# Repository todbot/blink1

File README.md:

blink(1) USB RGB LED
====================

"[blink(1)](https://blink1.thingm.com/) is a super status light:
it packs three dimensions of information
(color, brightness and pattern) into a single tiny package that fits into
any USB port on nearly every device. It makes it incredibly easy to connect
any data source in the cloud or on your computer to a full-color RGB LED so
you can know what's happening without checking any windows, going to any
websites or typing any commands." - Get a blink(1) at https://buy.thingm.com/

More technically, blink(1) is a Smart LED controller with built-in USB firmware. blink(1) has a huge range of support from the Linux kernel to Node.js.

The officially supported repositories for blink(1) software are:

| repository | description |
| ---------- | ----------- |
| [Blink1Control2](https://github.com/todbot/Blink1Control2) | Graphical app for Mac / Windows / Linux |
| [blink1-tool](https://github.com/todbot/blink1-tool) | Command-line tool, simple API server, and C-library for all platforms |
| [blink1-python](https://pypi.org/project/blink1/) | Python library |
| [blink1rs](https://crates.io/crates/blink1rs) | Rust library |
| [node-blink1](https://www.npmjs.com/package/node-blink1) | Node.js library |
| [blink1-java](https://github.com/todbot/blink1-java) | Java and Processing library |
| [go-blink1](https://github.com/todbot/go-blink1) | Go library |
| [blink1-android](https://github.com/todbot/blink1-android) | Android library |
| [blink1-webhid](https://github.com/todbot/blink1-webhid) | WebHID demos for blink(1) |
| [blink1mk3](https://github.com/todbot/blink1mk3) | Hardware/firmware design for blink(1) mk3 |
| [blink1](https://github.com/todbot/blink1) | Hardware/firmware design, misc docs & notes (this repo) |

Other instructive examples: 

| repository | description |
| ---------- | ----------- |
| [electron-blink1-toy](https://github.com/todbot/electron-blink1-toy/) | Simplest possible Electron app for controlling blink(1) |
| [tauri-blink1-toy](https://github.com/todbot/tauri-blink1-toy/) | Simplest possible Tauri/Rust app for controlling blink(1) |

See each project for details, including APIs for languages not mentioned.

This repo used to house all blink(1)-related code, but is now a clearinghouse and links to official and supported blink(1) repositories.

## Blink1Control2 ##

[Blink1Control2](https://github.com/todbot/Blink1Control2) is an application for controlling and hooking events to blink(1). It is the primary user-level application for controlling blink(1).
It is an event-based system for triggering blink(1) color patterns.
Those events can be on your computer or on the Net.

Blink1Control2 can receive events from:
- [IFTTT](https://ifttt.com/channels)'s many channels
- IMAP/GMAIL email services
- Skype events
- URLs containing text or JSON
- Local files or executed scripts

Blink1Control2 has its own repository. More information at:
https://github.com/todbot/Blink1Control2

#### Download Blink1Control2 ####
- Mac OS X: https://github.com/todbot/Blink1Control2/releases
- Windows: https://github.com/todbot/Blink1Control2/releases

## blink1-tool ##

`blink1-tool` is a C-based command-line for script-writers, programmers and hackers. It lives in the [blink1-tool repo]( https://github.com/todbot/blink1-tool):

The repo contains several useful tools:

- **blink1-tool** -- command-line program for use in your own scripts
- **blink1-tiny-server** -- simple RESTish JSON API server for controlling blink(1)s
- **blink1control-tool** -- control blink(1) through Blink1Controll app as if with blink1-tool

--- 

--- 

## What is in *this* repo ##

Most code in this repo is **deprecated** but kept around for historical interest.

- __docs__             -- Documentation of APIs and tips & tricks
- __java__             -- Java / Processing library info
- __processing__       -- Processing applications  (https://processing.org)
- __nodejs__           -- NodeJs library info
- __python__           -- Python libraries (there are a couple to choose from)
- __ruby__             -- Ruby APIs & Ruby Tools
- __go__               -- Go library
- __qt__               -- old Blink1Control1 Qt app
- __mac__              -- Mac OS X details and old Blink1Control0 app
  - scripts      -- command-line scripts to do cool things
- __windows__          -- Windows and .NET details and old Blink1Control0 app
  - Blink1Lib     -- .NET library wrapping blink1-lib 
  - ManagedBlink1 -- 100% .NET library, supercedd by [Sleddog.Blink1](https://github.com/SleddogSoftwareDevelopment/blink1)
  - scripts  -- Windows command-line scripts to do cool things
- __linux__            -- Linux details and scripts
  - contrib__    -- contributed Linux scripts
- __chrome__           -- ChromeOS info
- __hardware__         -- all hardware-related info (firmware & schematic & enclosure)

Useful docs
-------------

- [blink1-tool usage](https://github.com/todbot/blink1-tool/#commmand-line-options-for-blink1-tool)
- [app-url-api-examples](https://github.com/todbot/blink1/blob/master/docs/app-url-api-examples.md)
- [app-url-api](https://github.com/todbot/blink1/blob/master/docs/app-url-api.md)

Also see the [wiki pages](https://github.com/todbot/blink1/wiki/_pages)

# Copyright and License

blink(1) is open source hardware OSHW US000051

Copyright (c) ThingM, 2012-2018

'blink(1)' is a trademark of ThingM Corporation

License: CC BY-SA 3.0
https://creativecommons.org/licenses/by-sa/3.0/

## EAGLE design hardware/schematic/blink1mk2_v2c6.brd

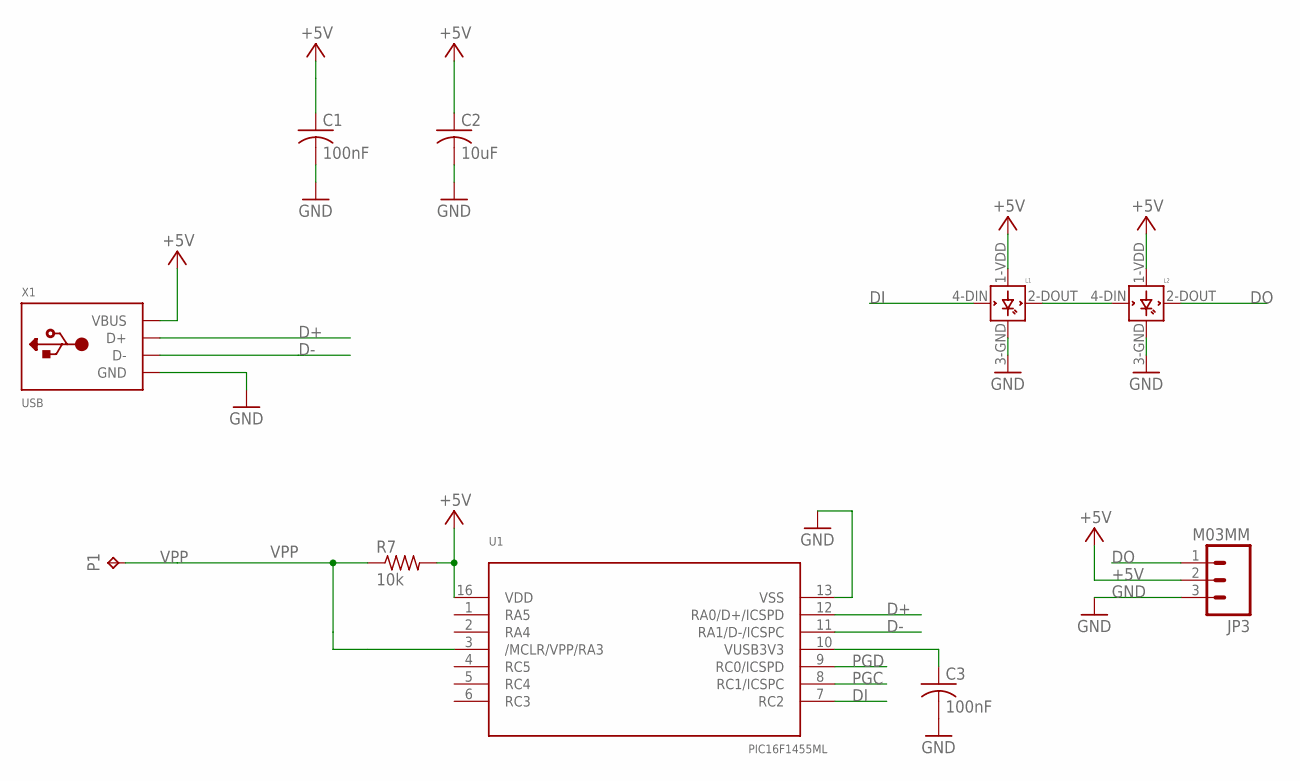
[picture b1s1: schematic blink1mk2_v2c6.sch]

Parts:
C1, C3: 100nF; C0603
C2: 10uF; C0603
JP3: M03MM; 1X03-1.5MM
L1, L2: WS2812B
P1: TPTP11SQ; TP11SQ
R7: 10k; R0603
U1: PIC16F1455ML; QFN16_4X4
X1: USB; MOLEX-48037-1000

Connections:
+5V: C1.1, C2.1, JP3.2, L1.1-VDD (VDD), L2.1-VDD (VDD), R7.2, U1.16 (VDD), X1.1 (VBUS)
D+: U1.12 (RA0/D+/ICSPD), X1.3 (D+)
D-: U1.11 (RA1/D-/ICSPC), X1.2 (D-)
DI: L1.4-DIN (DIN), U1.7 (RC2)
DO: JP3.1, L2.2-DOUT (DOUT)
GND: C1.2, C2.2, C3.2, JP3.3, L1.3-GND (GND), L2.3-GND (GND), U1.13 (VSS), X1.4 (GND)
unnamed: L1.2-DOUT (DOUT), L2.4-DIN (DIN)
PGC: U1.8 (RC1/ICSPC)
PGD: U1.9 (RC0/ICSPD)
VPP: P1.TP, R7.1, U1.3 (/MCLR/VPP/RA3)
VUSB3V3: C3.1, U1.10 (VUSB3V3)

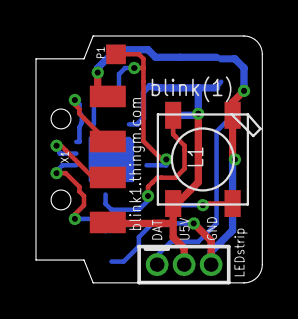
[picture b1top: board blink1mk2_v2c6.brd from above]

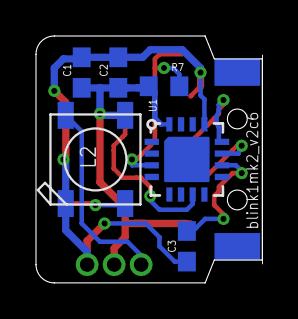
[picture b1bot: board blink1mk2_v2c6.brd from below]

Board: 2 copper layers, 12.6 x 13.7 mm, 10 parts (6 on the bottom side), 9 nets.

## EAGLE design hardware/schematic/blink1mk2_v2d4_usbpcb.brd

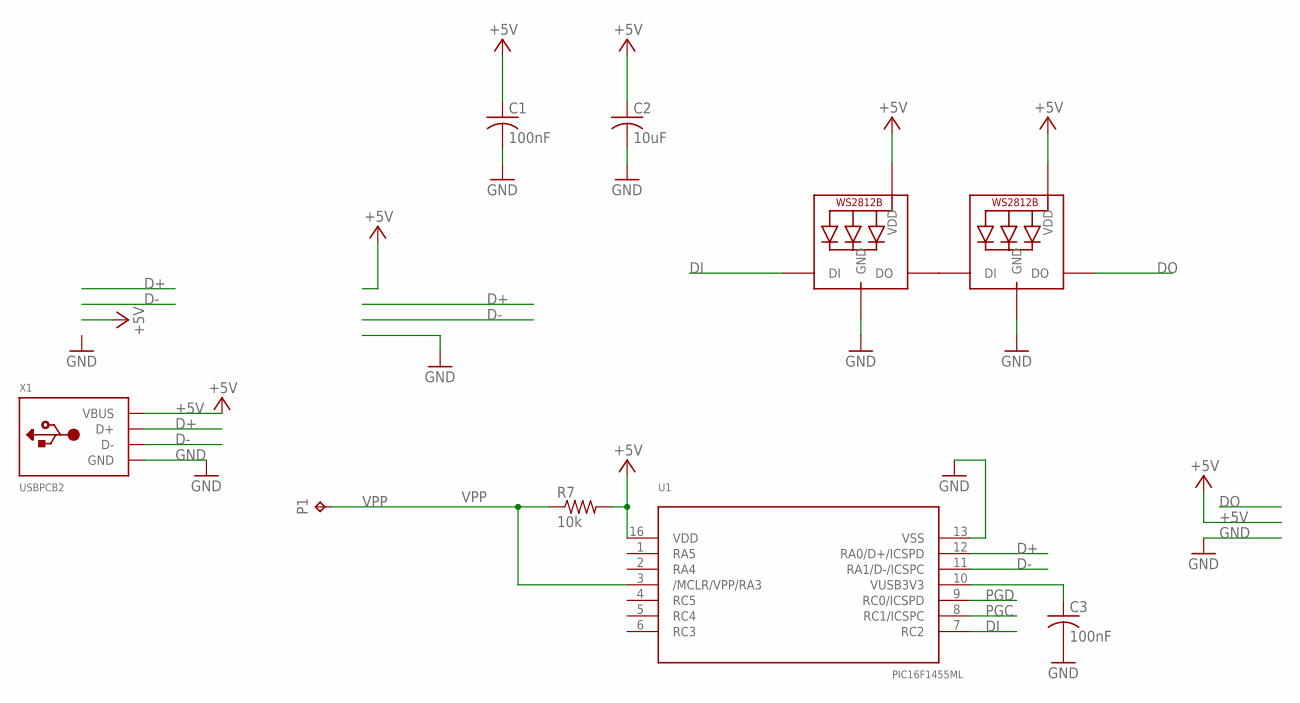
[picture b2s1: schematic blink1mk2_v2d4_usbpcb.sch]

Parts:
C1, C3: 100nF; C0603
C2: 10uF; C0603
LED1, LED2: WS2812B4020SIDE; SK6812-SIDE
P1: TPTP11SQ; TP11SQ
R7: 10k; R0603
U1: PIC16F1455ML; QFN16_4X4
X1: USBPCB2; USB-A-PCB-2

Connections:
+5V: C1.1, C2.1, LED1.1-VDD (VDD), LED2.1-VDD (VDD), R7.2, U1.16 (VDD), X1.5V (VBUS)
D+: U1.12 (RA0/D+/ICSPD), X1.USB_P (D+)
D-: U1.11 (RA1/D-/ICSPC), X1.USB_M (D-)
DI: LED1.4-DIN (DI), U1.7 (RC2)
DO: LED2.2-DOUT (DO)
GND: C1.2, C2.2, C3.2, LED1.3-GND (GND), LED2.3-GND (GND), U1.13 (VSS), X1.GND
unnamed: LED1.2-DOUT (DO), LED2.4-DIN (DI)
PGC: U1.8 (RC1/ICSPC)
PGD: U1.9 (RC0/ICSPD)
VPP: P1.TP, R7.1, U1.3 (/MCLR/VPP/RA3)
VUSB3V3: C3.1, U1.10 (VUSB3V3)

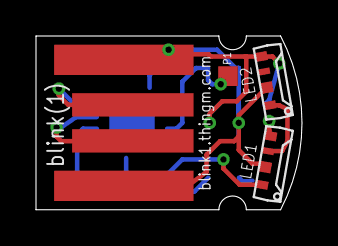
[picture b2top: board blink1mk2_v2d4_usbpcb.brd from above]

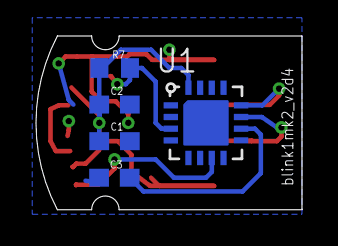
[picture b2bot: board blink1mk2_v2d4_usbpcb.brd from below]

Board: 2 copper layers, 14.8 x 9.7 mm, 9 parts (5 on the bottom side), 8 nets.

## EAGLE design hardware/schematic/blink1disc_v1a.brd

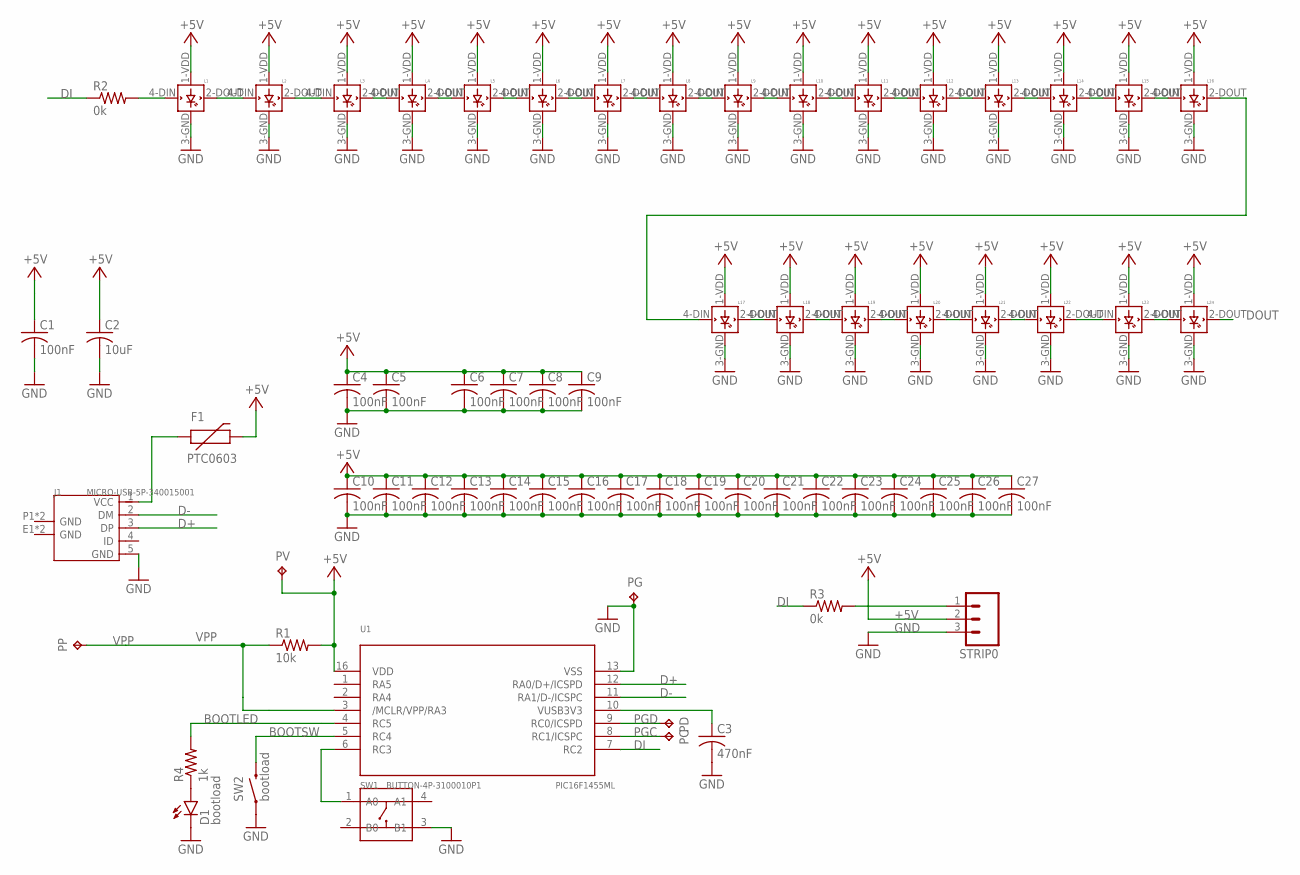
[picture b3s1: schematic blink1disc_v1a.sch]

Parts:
C1, C4, C5, C6, C7, C8, C9, C10, C11, C12, C13, C14, C15, C16, C17, C18, C19, C20, C21, C22, C23, C24, C25, C26, C27: 100nF; C0603
C2: 10uF; C0603
C3: 470nF; C0603
D1: bootload; LED-0603
F1: PTC0603; 0603
J1: MICRO-USB-5P-340015001; B-SMD-5P
L1, L2, L3, L4, L5, L6, L7, L8, L9, L10, L11, L12, L13, L14, L15, L16, L17, L18, L19, L20, L21, L22, L23, L24: WS2812B
PC: TPTP11SQ; TP11SQ
PD: TPTP11SQ; TP11SQ
PG: TPTP11SQ; TP11SQ
PP: TPTP11SQ; TP11SQ
PV: TPTP11SQ; TP11SQ
R1: 10k; R0603
R2, R3: 0k; R0603
R4: 1k; R0603
STRIP0: M03PTH; 1X03
SW1: BUTTON-4P-3100010P1; 4P-SMD-6.0X6.0X5.0H
SW2: bootload; TACTILE_SWITCH-SMD-RIGHT-ANGLE
U1: PIC16F1455ML; QFN16_4X4

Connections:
+5V: C1.1, C2.1, C4.1, C5.1, C6.1, C7.1, C8.1, C9.1, C10.1, C11.1, C12.1, C13.1, C14.1, C15.1, C16.1, C17.1, C18.1, C19.1, C20.1, C21.1, C22.1, C23.1, C24.1, C25.1, C26.1, C27.1, F1.2, L1.1-VDD (VDD), L2.1-VDD (VDD), L3.1-VDD (VDD), L4.1-VDD (VDD), L5.1-VDD (VDD), L6.1-VDD (VDD), L7.1-VDD (VDD), L8.1-VDD (VDD), L9.1-VDD (VDD), L10.1-VDD (VDD), L11.1-VDD (VDD), L12.1-VDD (VDD), L13.1-VDD (VDD), L14.1-VDD (VDD), L15.1-VDD (VDD), L16.1-VDD (VDD), L17.1-VDD (VDD), L18.1-VDD (VDD), L19.1-VDD (VDD), L20.1-VDD (VDD), L21.1-VDD (VDD), L22.1-VDD (VDD), L23.1-VDD (VDD), L24.1-VDD (VDD), PV.TP, R1.2, STRIP0.2, U1.16 (VDD)
BOOTLED: R4.2, U1.4 (RC5)
BOOTSW: SW2.2, U1.5 (RC4)
D+: J1.3 (DP), U1.12 (RA0/D+/ICSPD)
D-: J1.2 (DM), U1.11 (RA1/D-/ICSPC)
DI: R2.1, R3.1, U1.7 (RC2)
DO1: L2.2-DOUT (DOUT), L3.4-DIN (DIN)
DOUT: L24.2-DOUT (DOUT)
GND: C1.2, C2.2, C3.2, C4.2, C5.2, C6.2, C7.2, C8.2, C9.2, C10.2, C11.2, C12.2, C13.2, C14.2, C15.2, C16.2, C17.2, C18.2, C19.2, C20.2, C21.2, C22.2, C23.2, C24.2, C25.2, C26.2, C27.2, D1.C, J1.5 (GND), L1.3-GND (GND), L2.3-GND (GND), L3.3-GND (GND), L4.3-GND (GND), L5.3-GND (GND), L6.3-GND (GND), L7.3-GND (GND), L8.3-GND (GND), L9.3-GND (GND), L10.3-GND (GND), L11.3-GND (GND), L12.3-GND (GND), L13.3-GND (GND), L14.3-GND (GND), L15.3-GND (GND), L16.3-GND (GND), L17.3-GND (GND), L18.3-GND (GND), L19.3-GND (GND), L20.3-GND (GND), L21.3-GND (GND), L22.3-GND (GND), L23.3-GND (GND), L24.3-GND (GND), PG.TP, STRIP0.3, SW1.3 (B1), SW2.1, U1.13 (VSS)
unnamed: L3.2-DOUT (DOUT), L4.4-DIN (DIN)
unnamed: L1.2-DOUT (DOUT), L2.4-DIN (DIN)
unnamed: L5.2-DOUT (DOUT), L6.4-DIN (DIN)
unnamed: L4.2-DOUT (DOUT), L5.4-DIN (DIN)
unnamed: L7.2-DOUT (DOUT), L8.4-DIN (DIN)
unnamed: L9.2-DOUT (DOUT), L10.4-DIN (DIN)
unnamed: L8.2-DOUT (DOUT), L9.4-DIN (DIN)
unnamed: L11.2-DOUT (DOUT), L12.4-DIN (DIN)
unnamed: L13.2-DOUT (DOUT), L14.4-DIN (DIN)
unnamed: L12.2-DOUT (DOUT), L13.4-DIN (DIN)
unnamed: L1.4-DIN (DIN), R2.2
unnamed: R3.2, STRIP0.1
unnamed: L15.2-DOUT (DOUT), L16.4-DIN (DIN)
unnamed: L14.2-DOUT (DOUT), L15.4-DIN (DIN)
unnamed: SW1.1 (A0), U1.6 (RC3)
unnamed: L6.2-DOUT (DOUT), L7.4-DIN (DIN)
unnamed: L17.2-DOUT (DOUT), L18.4-DIN (DIN)
unnamed: D1.A, R4.1
unnamed: L19.2-DOUT (DOUT), L20.4-DIN (DIN)
unnamed: L18.2-DOUT (DOUT), L19.4-DIN (DIN)
unnamed: L21.2-DOUT (DOUT), L22.4-DIN (DIN)
unnamed: L20.2-DOUT (DOUT), L21.4-DIN (DIN)
unnamed: L23.2-DOUT (DOUT), L24.4-DIN (DIN)
unnamed: L22.2-DOUT (DOUT), L23.4-DIN (DIN)
unnamed: L16.2-DOUT (DOUT), L17.4-DIN (DIN)
unnamed: L10.2-DOUT (DOUT), L11.4-DIN (DIN)
PGC: PC.TP, U1.8 (RC1/ICSPC)
PGD: PD.TP, U1.9 (RC0/ICSPD)
VPP: PP.TP, R1.1, U1.3 (/MCLR/VPP/RA3)
VUSB: F1.1, J1.1 (VCC)
VUSB3V3: C3.1, U1.10 (VUSB3V3)

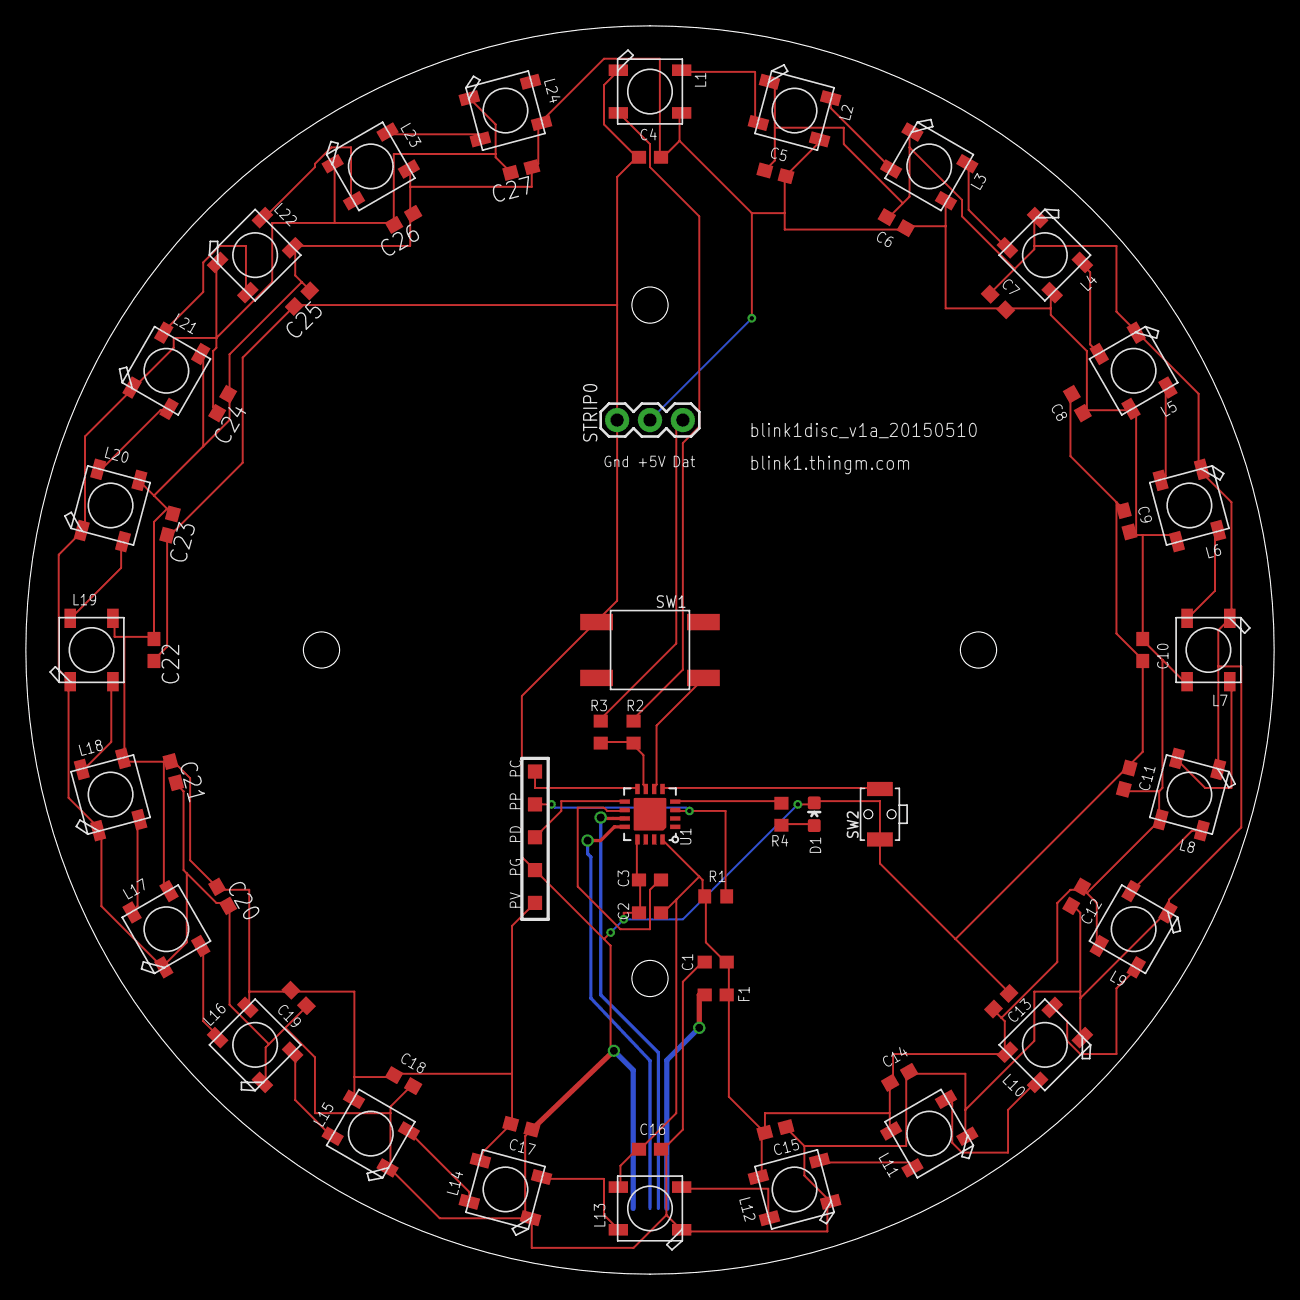
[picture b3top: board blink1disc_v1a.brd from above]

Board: 2 copper layers, 96.5 x 96.5 mm, 67 parts (1 on the bottom side), 39 nets.

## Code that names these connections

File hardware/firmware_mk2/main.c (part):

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 *
 * pin 1  - RA5            - n/c
 * pin 2  - RA4            - n/c
 * pin 3  - RA3/MCLR/VPP   - VPP testpad, 10k pullup to VDD
 * pin 4  - RC5            - n/c
 * pin 5  - RC4            - n/c
 * pin 6  - RC3            - n/c
 * pin 7  - RC2            - WS2811 serial out (to DI pin on LED1)
 * pin 8  - RC1            - n/c
 * pin 9  - RC0            - n/c
 * pin 10 - VUSB3V3        - 100nF cap to Gnd
 * pin 11 - RA1/D-/ICSPC   - D-  on USB
 * pin 12 - RA0/D+/ICSPD   - D+  on USB
 * pin 13 - VSS            - Gnd on USB
 * pin 14 - n/c            - n/c
 * pin 15 - n/c            - n/c
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
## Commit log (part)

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2017-07-18 re-enabled blink1-tiny-server compilation in appveyor
2017-07-18 fix windows build of blink1-tiny-server
2017-07-18 re-enable blink1control-tool on windows appveyor build
2017-07-18 attempt to get json-parser to compile in appveyor
2017-07-18 removed json-parser from gitmodules, stuck in zip file, because appveyor msys2 cannot handle unixy-paths it seems. sigh. Now be sure to do "make json-parser-setup" before compiling blink1control-tool
2017-07-18 oops, forgot to add json-parser.zip
2017-07-18 added json-parser-setup to blink1control-tool build
2017-07-18 added zip unzip note in Makefile for blink1 tool compiles
2017-07-19 blink1control-tool: fix warnings a bit by breaking things
2017-07-19 updated mongoose
2017-07-21 try out s3 deploy on both travis and appveyor
2017-08-24 updated README to be more clear about Blink1Control2
2017-10-17 blink1-tiny-server: fixes for some uris (/blink1/red, etc) not returning responses
2017-12-01 added serialization list for 2017Q4 seeed production run
2018-01-09 update udev rules exmaple for hidraw
2018-02-21 linux/contrib: Make `ippontv-to-blink.pl` executable
    Add the executable bit for the Perl script `ippontv-to-blink.pl`, so it
    can be run directly.
2018-02-21 http to https per issue #322
2018-03-20 test pcb usb jack layouts
2018-03-22 added support for alternate USB HID reportids
2018-03-22 added last rgb value ability
2018-03-22 update production ids for seeed 2017
2018-03-22 update gitignore (not sure why the change is so big)
2018-03-22 update firmware_mk2 project after attempting to compile it with later MPLAB
2018-03-23 added readNote/writeNote commands for potental mk3 device
2018-04-15 update license
2018-04-18 added lockstate-{get,test} scripts for Windows for use with Blink1Control2
2018-04-19 update python README to point to real blink1-python lib
2018-04-20 fix longstanding servertickle/serverdown max time bug #289, add new serverdown feature to play its own subloop #335
2018-04-20 firmware: fix small USB descriptor bug that caused warnings in Linux
2018-04-25 added 2018Q1 hex and serialization notes
2018-04-29 started README and repo rework
2018-04-29 update README, remove commandline dir since now blink1-tool
2018-08-16 fix #339, update bad links for blink1-tool download
2018-08-16 linux: add note about kernel support
2018-08-16 update serials for seeed 2018Q1 run
2018-08-16 small readme update
2018-08-16 added logo
2019-05-02 update README to point to mk3 repo
2019-07-27 update command table
2019-08-04 Add systemd unit for running blink1-tiny-server
    Adds a template unit to enable running blink1-tiny-server under systemd.
2019-08-05 Add systemd unit for running blink1-tiny-server (#346)
    Adds a template unit to enable running blink1-tiny-server under systemd.
2019-09-13 Delete blink1test1.js
    Loß all die false connection falle!
2019-10-08 added Rust library link. issue #644. thx @dadleyy!
2019-10-22 added blink1-webhid demos link
2020-02-17 small update to blink1-hid-commands
2020-02-17 simplify udev 51-blink1.rules
2020-02-22 added link to blink1-android library
2020-03-04 update location of blink1-java library
2020-03-04 update location of Processing library
2020-08-09 Adding FreeBSD README.md and devd rules
2020-08-09 Freebsd devd rules (#655)
    * Adding FreeBSD README.md and devd rules
    * Update README.md
2020-11-06 update license to CC-BY-SA-4.0, issue #337
2021-12-27 add example project using node-blink1
2021-12-30 add example project using node-blink1 (#665)
2022-06-03 Add systemd service: indicate status via blink(1)
    This is useful with headless systems: it lights the blink(1) up in
    green when the system is up and sshd has been started, turns the light
    red when the system is shutting down, and lets you know that the
    system has powered off when the light goes dark.
2022-06-03 Add systemd service: indicate status via blink(1) (#666)
    This is useful with headless systems: it lights the blink(1) up in
    green when the system is up and sshd has been started, turns the light
    red when the system is shutting down, and lets you know that the
    system has powered off when the light goes dark.
2022-08-27 update readme about .NET, update openwrt instructions
2022-09-07 note about Blink1DotNet
2025-11-20 update api docs and links to blink1-tool
2025-11-20 clarify /blink1/pattern endpoint name

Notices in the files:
parts and their libraries:
SparkFun-Connectors: Licensing: Creative Commons ShareAlike 4.0 International - https://creativecommons.org/licenses/by-sa/4.0
